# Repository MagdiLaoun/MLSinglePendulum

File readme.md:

# Readme
This repository contains all the files needed to build a simple pendulum.
- **Inverted pendulum (English).pdf**: theory of pendulum kinematics and balance control, English version
- **Inverted pendulum (French).pdf**: theory of pendulum kinematics and balance control, French version
- **ComponentList.md**: Bill of material of the machine
- **Single Pendulum STL**: Folder containing all the 3D-print parts in stl format
- **Single Pendulum Circuit**: Folder containing the pcb (schematic + footprint) drawn on Kicad, this circuit allows to connect electrically all the parts together (motor, controller, etc.)
- **Single Pendulum C++**: Folder containing the source code of the controller, written in C++, in VSCode PlatformIO
- **Single Pendulum SwiftUI**: Folder containing the source code of the program on the computer to set-up the system, to set the parameters and to launch the machine, written in SwiftUI, for MacOS computer

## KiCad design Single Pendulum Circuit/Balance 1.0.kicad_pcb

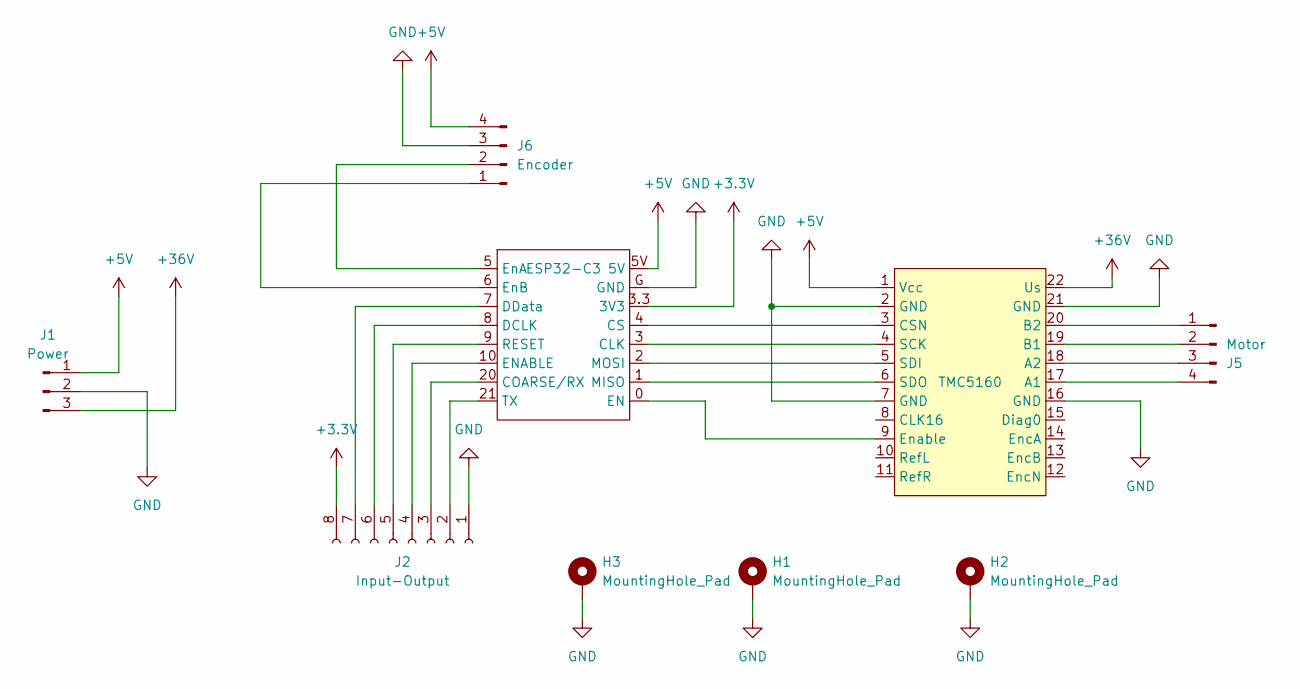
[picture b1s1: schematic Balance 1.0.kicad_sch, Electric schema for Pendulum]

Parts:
H1, H2, H3: MountingHole_Pad; MountingHole_3.2mm_M3_DIN965_Pad
J1: Power; JST_XH_B3B-XH-AM_1x03_P2.50mm_Vertical
J2: Input-Output; PinSocket_1x08_P2.54mm_Vertical
J5: Motor; PinHeader_1x04_P2.54mm_Vertical
J6: Encoder; PinSocket_1x04_P2.54mm_Vertical
U1: TMC5160
U2: ESP32-C3; ESP32C3

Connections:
+3.3V: J2.8, U2.3.3 (3V3)
+5V: J1.1, J6.4, U1.1 (Vcc), U2.5V
+36V: J1.3, U1.22 (Us)
GND: H1.1, H2.1, H3.1, J1.2, J2.1, J6.3, U1.2 (GND), U1.7 (GND), U1.16 (GND), U1.21 (GND), U2.G (GND)
unnamed: J2.2, U2.21 (TX)
unnamed: J2.3, U2.20 (COARSE/RX)
unnamed: J2.4, U2.10 (ENABLE)
unnamed: J2.5, U2.9 (RESET)
unnamed: J2.6, U2.8 (DCLK)
unnamed: J2.7, U2.7 (DData)
unnamed: J5.1, U1.20 (B2)
unnamed: J5.2, U1.19 (B1)
unnamed: J5.3, U1.18 (A2)
unnamed: J5.4, U1.17 (A1)
unnamed: J6.1, U2.6 (EnB)
unnamed: J6.2, U2.5 (EnA)
unnamed: U1.3 (CSN), U2.4 (CS)
unnamed: U1.9 (Enable), U2.0 (EN)
unnamed: U1.4 (SCK), U2.3 (CLK)
unnamed: U1.5 (SDI), U2.2 (MOSI)
unnamed: U1.6 (SDO), U2.1 (MISO)

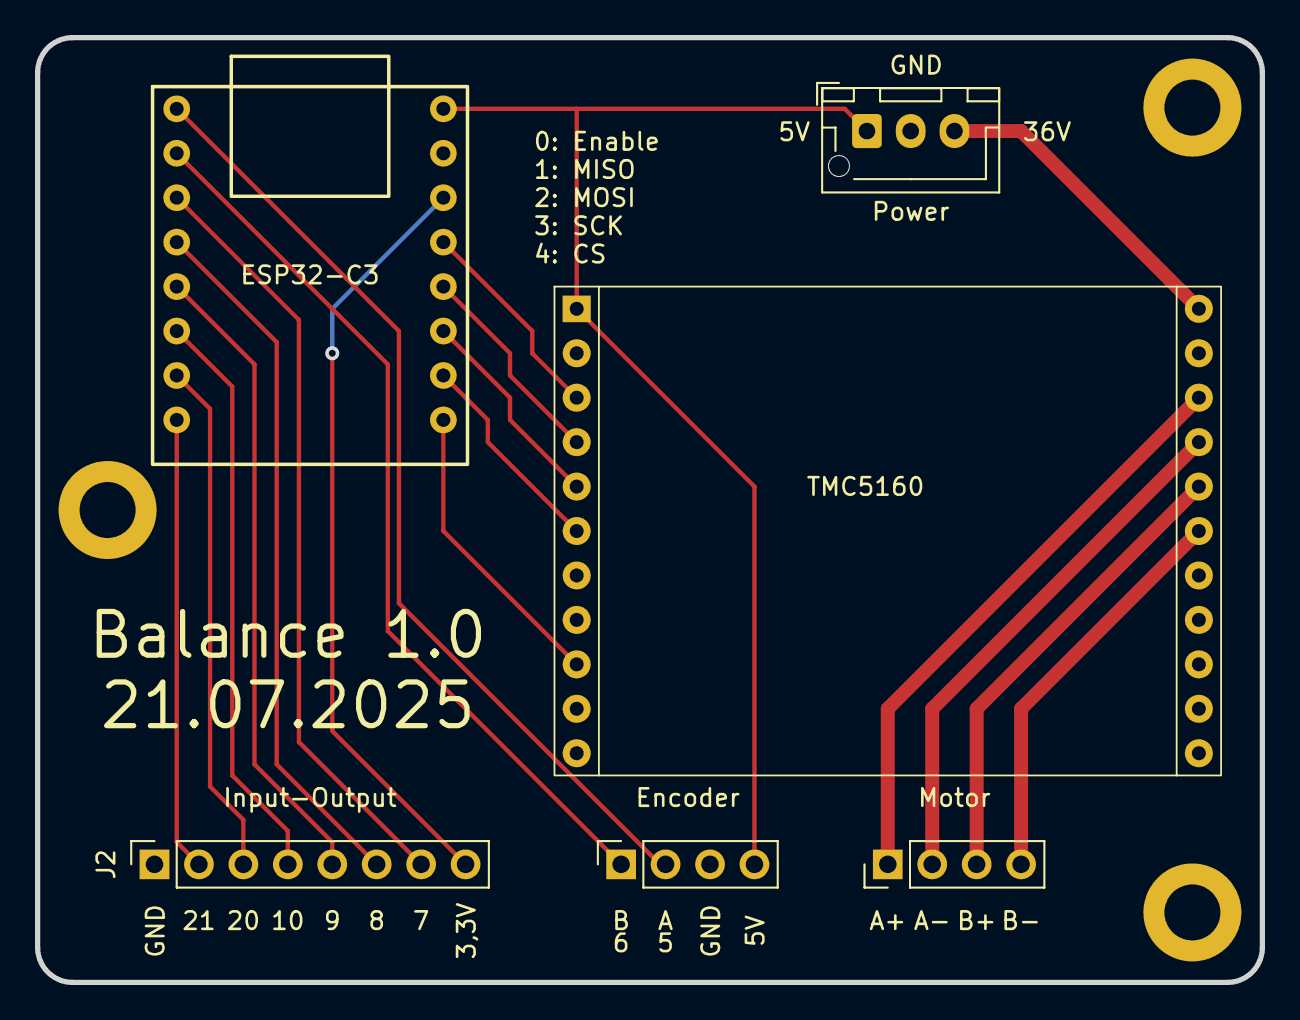
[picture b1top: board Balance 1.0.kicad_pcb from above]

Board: 2 copper layers, 70.0 x 54.0 mm, 9 parts (0 on the bottom side), 21 nets.

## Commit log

2026-05-23 adding stl files
2026-05-23 update bill of material
2026-05-23 Update of files
2026-05-23 Update files
